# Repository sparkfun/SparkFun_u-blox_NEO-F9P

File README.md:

SparkFun GNSS-RTK L1/L5 Breakout - NEO-F9P (Qwiic)
========================================

[*SparkFun GNSS-RTK L1/L5 Breakout - NEO-F9P (Qwiic) (GPS-23288)*](https://www.sparkfun.com/products/23288)

The SparkFun GNSS-RTK L1/L5 Breakout - NEO-F9P (Qwiic) is a high-precision GNSS board with equally impressive configuration options. The NEO-F9P is an upgrade to the NEO-M8P and utilizes the L1/L5 bands instead of the L1/L2 bands. Utilizing the L5 band, the NEO-F9P delivers improved performance under challenging urban environments because the L5 signals fall within the protected ARNS (aeronautical radio navigation service) frequency band. This band is less subject to RF interference.

The NEO-F9P module is a powerful 184-channel u-blox F9 engine GNSS receiver, meaning it can receive signals from the GPS, GLONASS, Galileo, and BeiDou constellations with 10mm, three-dimensional accuracy! That's right; such accuracy can be achieved with an RTK navigation solution when used with a correction source. With this board, you will be able to know where your (or any object's) X, Y, and Z location is within roughly the width of your fingernail! The module supports the concurrent reception of four GNSS systems. This module features a survey-in mode, allowing the module to become a base station and produce RTCM 3.x correction data.

We've included a rechargeable backup battery to keep the latest module configuration and satellite data available for up to two weeks. This battery helps 'warm-start' the module, decreasing the time-to-first-fix dramatically from a cold start of ~27s down to a hot start of ~3s. The battery will maintain RTC and GNSS orbit data without being connected to power for plenty of time. We have included an SMA connector for a secure connection.

The GNSS-RTK even has five communications ports, which are all active simultaneously: USB-C (which enumerates as a COM port), UART1 (with 3.3V TTL), UART2 for RTCM reception (with 3.3V TTL), I<sup>2</sup>C, and SPI. Utilizing our handy Qwiic system, no soldering is required to connect it to the rest of your system. However, we still have broken out 0.1"-spaced pins if you prefer a breadboard.

u-blox-based GPS products are configurable using the popular but dense Windows program u-center. Many different functions can be configured on the NEO-F9P: baud rates, update rates, geofencing, spoofing detection, external interrupts, SBAS/D-GNSS, increasing the high precision RTK solution to 20Hz, etc. All of this can be done within the SparkFun Arduino Library!

Our extensive [Arduino Library for u-blox modules](https://github.com/sparkfun/SparkFun_u-blox_GNSS_v3) makes reading and controlling the GNSS-RTK over our [Qwiic Connect System](https://www.sparkfun.com/qwiic) easy. Leave NMEA behind! Start using a much lighter-weight binary interface and give your microcontroller a break. The SparkFun Arduino library shows how to read latitude, longitude, even heading, and speed over I<sup>2</sup>C without constant serial polling.

Repository Contents
-------------------

* **/Hardware** - Eagle design files (.brd, .sch)

Documentation
--------------

* [**Installing an Arduino Library Guide**](https://learn.sparkfun.com/tutorials/installing-an-arduino-library) - Basic information on how to install an Arduino library.
* **[Library](https://github.com/sparkfun/SparkFun_u-blox_GNSS_v3/)** - Arduino library for the NEO-F9P.
* **[Hookup Guide](http://docs.sparkfun.com/SparkFun_u-blox_NEO-F9P/)** - Basic hookup guide for the NEO-F9P breakout board.

Product Versions
----------------

* [GPS-23288](https://www.sparkfun.com/products/23288) - Initial release

Version History
---------------
* v1.1 - Initial release

License Information
-------------------

This product is _**open source**_!

Please review the LICENSE.md file for license information.

If you have any questions or concerns on licensing, please contact technical support on our [SparkFun forums](https://forum.sparkfun.com/viewforum.php?f=152).

Distributed as-is; no warranty is given.

- Your friends at SparkFun.

_<COLLABORATION CREDIT>_

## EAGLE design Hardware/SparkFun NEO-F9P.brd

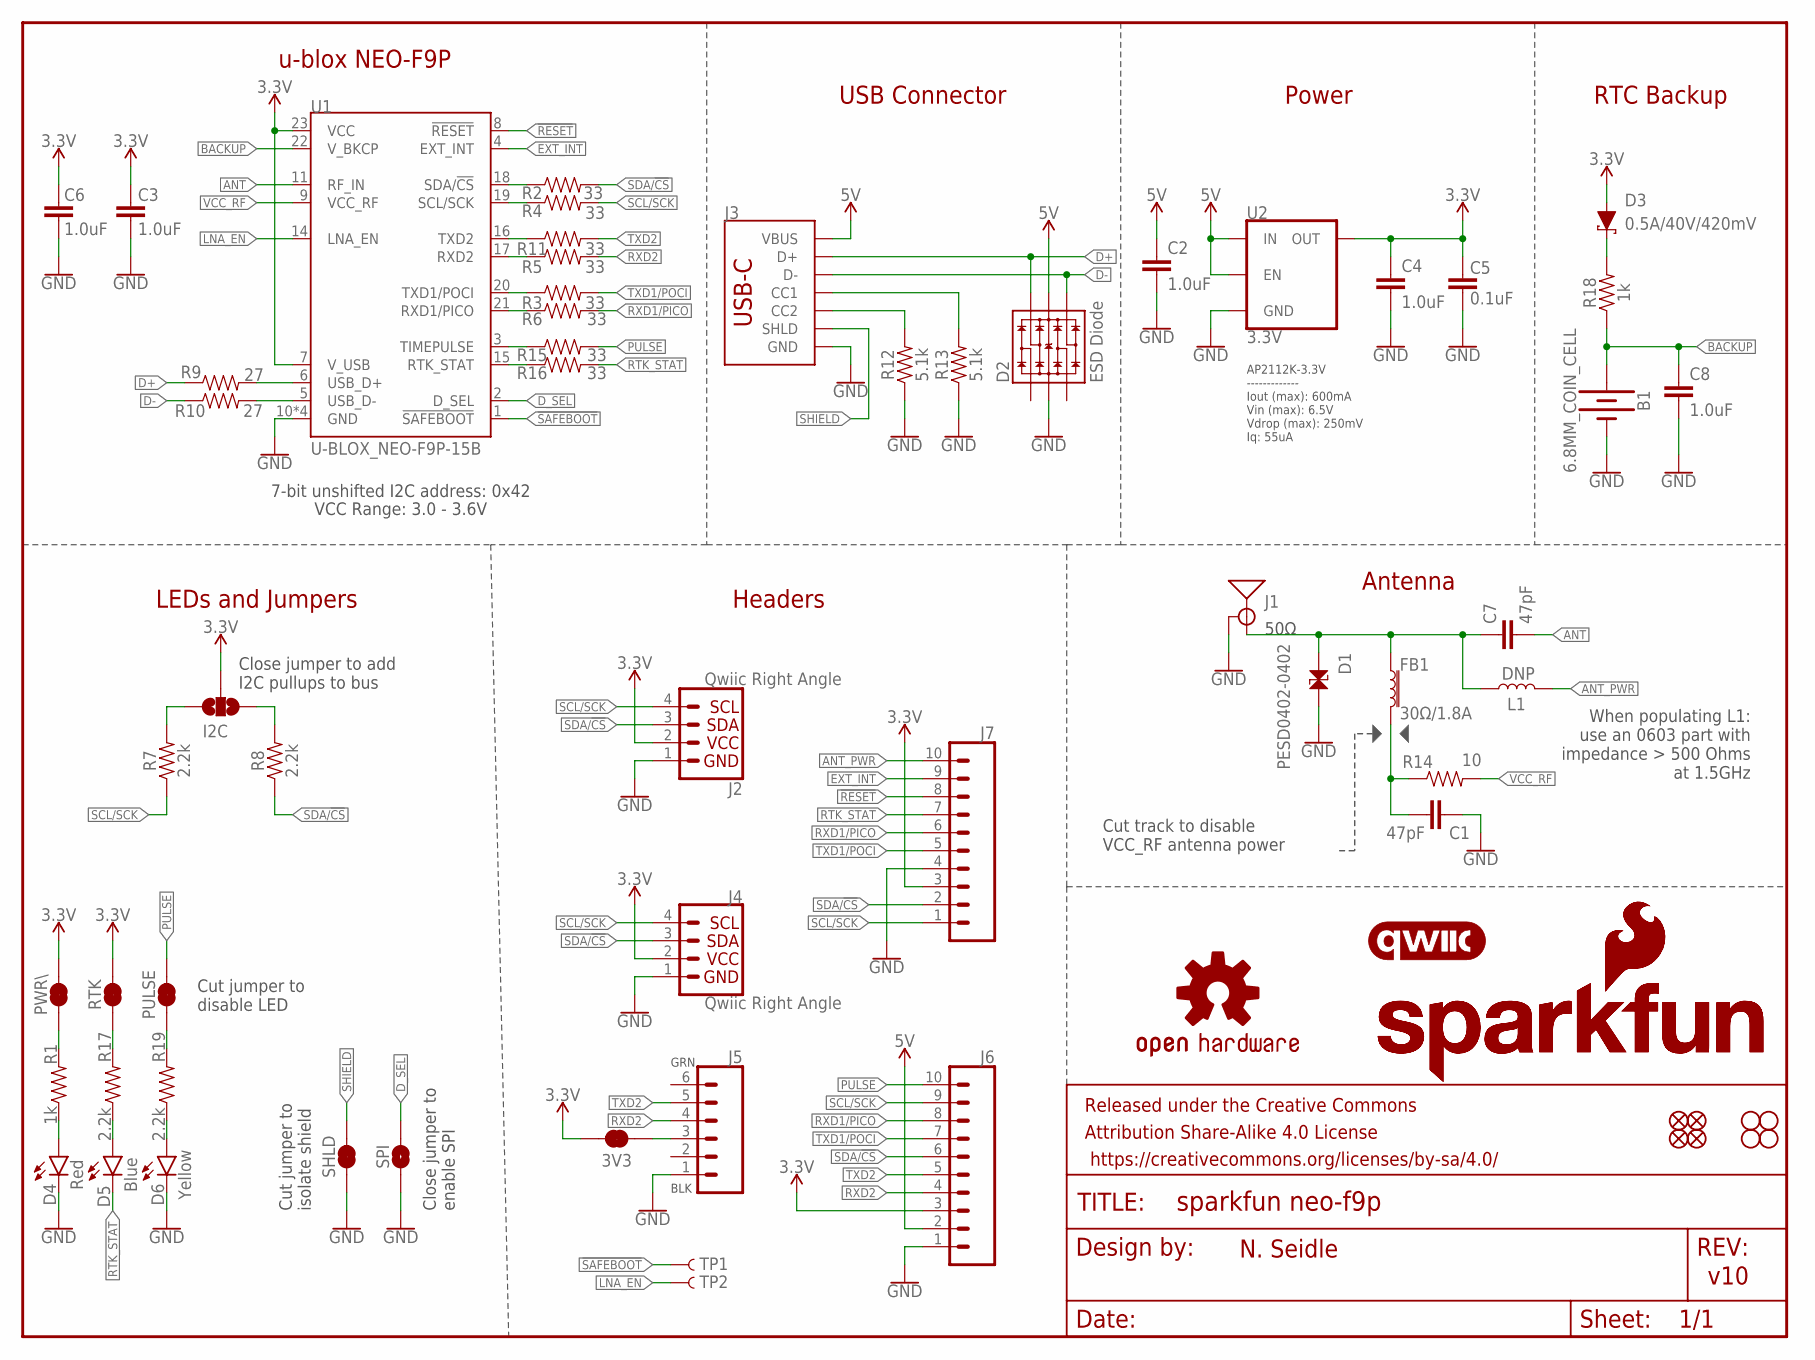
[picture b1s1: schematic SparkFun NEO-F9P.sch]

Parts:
3V3: JUMPER-SMT_2_NC_TRACE_SILK; SMT-JUMPER_2_NC_TRACE_SILK
B1: 6.8MM_COIN_CELL; ML414H_IV01E
C1, C7: 47pF; 0603
C2, C3, C4, C6, C8: 1.0uF; 0603
C5: 0.1uF; 0603
D1: PESD0402-0402; 0402
D2: ESD Diode; SOT-23-6
D3: 0.5A/40V/420mV; SOD-323
D4: Red; LED-0603
D5: Blue; LED-0603
D6: Yellow; LED-0603
FB1: 30Ω/1.8A; 0603
FRAME1: FRAME-LETTER; CREATIVE_COMMONS
I2C: JUMPER-SMT_3_NO_SILK; SMT-JUMPER_3_NO_SILK
J1: ANTENNA-SMA-GROUNDEDEDGE_SMA; SMA-EDGE
J2, J4: Qwiic Right Angle; JST04_1MM_RA
J3: USB_C_2-LAYER_PADS; USB-C-16P-2LAYER-PADS
J5: CONN_06NO_SILK_FEMALE_PTH; 1X06_NO_SILK
J6, J7: CONN_10NO_SILK_PTH_FEMALE; 1X10_NO_SILK
JP21, JP61, JP71, JP81: FIDUCIALUFIDUCIAL; MICRO-FIDUCIAL
JP31, JP41, JP91, JP101: STAND-OFF
L1: DNP; 0603_NO-CREAM
LOGO2: SFE_LOGO_NAME_FLAME.1_INCH; SFE_LOGO_NAME_FLAME_.1
LOGO3: SFE_LOGO_NAME_FLAME7_MM; SFE_LOGO_NAME_FLAME_7MM
LOGO4: OSHW-LOGOS; OSHW-LOGO-S
LOGO5: QWIIC_LOGO_5MM; QWIIC_5MM
PULSE: JUMPER-SMT_2_NC_TRACE_SILK; SMT-JUMPER_2_NC_TRACE_SILK
PWR\: JUMPER-SMT_2_NC_TRACE_SILK; SMT-JUMPER_2_NC_TRACE_SILK
R1, R18: 1k; 0603
R2, R3, R4, R5, R6, R11, R15, R16: 33; 0603
R7, R8, R17, R19: 2.2k; 0603
R9, R10: 27; 0603
R12, R13: 5.1k; 0603
R14: 10; 0603
RTK: JUMPER-SMT_2_NC_TRACE_SILK; SMT-JUMPER_2_NC_TRACE_SILK
SHLD: JUMPER-SMT_2_NC_TRACE_SILK; SMT-JUMPER_2_NC_TRACE_SILK
SPI: JUMPER-SMT_2_NO_SILK; SMT-JUMPER_2_NO_SILK
TP1, TP2: TEST-POINTPOGO_PTH; 1X01_NO_SILK
U1: U-BLOX_NEO-F9P-15B; NEO-M9N/M8T/M8U/D9S/F9P
U2: 3.3V; SOT23-5

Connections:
3.3V: 3V3.2, C3.1, C4.1, C5.2, C6.1, D3.A, I2C.2, J2.2, J4.2, J6.3, J7.3, PWR\.2, RTK.2, U1.7 (V_USB), U1.23 (VCC), U2.5 (OUT)
5V: C2.1, D2.5 (VCC), J3.VBUS1 (VBUS), J3.VBUS2 (VBUS), J6.2, U2.1 (IN), U2.3 (EN)
!RESET!: J7.8, U1.8 (!RESET!)
!SAFEBOOT!: TP1.1, U1.1 (!SAFEBOOT!)
ANT: C7.2, U1.11 (RF_IN)
ANT_PWR: J7.10, L1.2
ANT_VCC: C1.1, FB1.2, R14.1
BACKUP: B1.+, C8.1, R18.1, U1.22 (V_BKCP)
D+: D2.6 (IO4), J3.A6 (D+), J3.B6 (D+), R9.1
D-: D2.4 (IO3), J3.A7 (D-), J3.B7 (D-), R10.1
D_SEL: SPI.2, U1.2 (D_SEL)
EXT_INT: J7.9, U1.4 (EXT_INT)
GND: B1.-, C1.2, C2.2, C3.2, C4.2, C5.1, C6.2, C8.2, D1.2, D2.2 (VSS), D4.C, D6.C, J1.GND@0 (GND), J1.GND@1 (GND), J1.GND@2 (GND), J1.GND@3 (GND), J2.1, J3.GND, J3.GND2 (GND), J4.1, J5.1, J6.1, J7.4, R12.1, R13.1, SHLD.1, SPI.1, U1.10 (GND), U1.12 (GND), U1.13 (GND), U1.24 (GND), U2.2 (GND)
LNA_EN: TP2.1, U1.14 (LNA_EN)
unnamed: PWR\.1, R1.2
unnamed: R3.1, U1.20 (TXD1/POCI)
unnamed: R2.1, U1.18 (SDA/!CS!)
unnamed: R4.1, U1.19 (SCL/SCK)
unnamed: I2C.1, R8.2
unnamed: R6.1, U1.21 (RXD1/PICO)
unnamed: J3.B5 (CC2), R12.2
unnamed: I2C.3, R7.2
unnamed: J3.A5 (CC1), R13.2
unnamed: D4.A, R1.1
unnamed: R9.2, U1.6 (USB_D+)
unnamed: R10.2, U1.5 (USB_D-)
unnamed: 3V3.1, J5.3
unnamed: R11.1, U1.16 (TXD2)
unnamed: R5.1, U1.17 (RXD2)
unnamed: R15.1, U1.3 (TIMEPULSE)
unnamed: R16.1, U1.15 (RTK_STAT)
unnamed: D5.A, R17.1
unnamed: R17.2, RTK.1
unnamed: D3.C, R18.2
unnamed: D6.A, R19.1
unnamed: PULSE.1, R19.2
PULSE: J6.10, PULSE.2, R15.2
RTK_STAT: D5.C, J7.7, R16.2
RXD1/PICO: J6.8, J7.6, R6.2
RXD2: J5.4, J6.4, R5.2
SCL/SCK: J2.4, J4.4, J6.9, J7.1, R4.2, R7.1
SDA/!CS!: J2.3, J4.3, J6.6, J7.2, R2.2, R8.1
SHIELD: J3.SHLD1 (SHLD), J3.SHLD2 (SHLD), J3.SHLD3 (SHLD), J3.SHLD4 (SHLD), SHLD.2
SMA: C7.1, D1.1, FB1.1, J1.SIG (SIGNAL), L1.1
TXD1/POCI: J6.7, J7.5, R3.2
TXD2: J5.5, J6.5, R11.2
VCC_RF: R14.2, U1.9 (VCC_RF)

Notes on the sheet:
v10
7-bit unshifted I2C address: 0x42
Close jumper to add I2C pullups to bus
Cut jumper to disable LED
Close jumper to enable SPI
N. Seidle
Headers
LEDs and Jumpers
u-blox NEO-F9P
Antenna
USB Connector
VCC Range: 3.0 - 3.6V
BLK
GRN
Cut jumper to isolate shield
50Ω
Cut track to disable VCC_RF antenna power
When populating L1: use an 0603 part with impedance > 500 Ohms at 1.5GHz
AP2112K-3.3V ------------- Iout (max): 600mA Vin (max): 6.5V Vdrop (max): 250mV Iq: 55uA
RTC Backup
Power

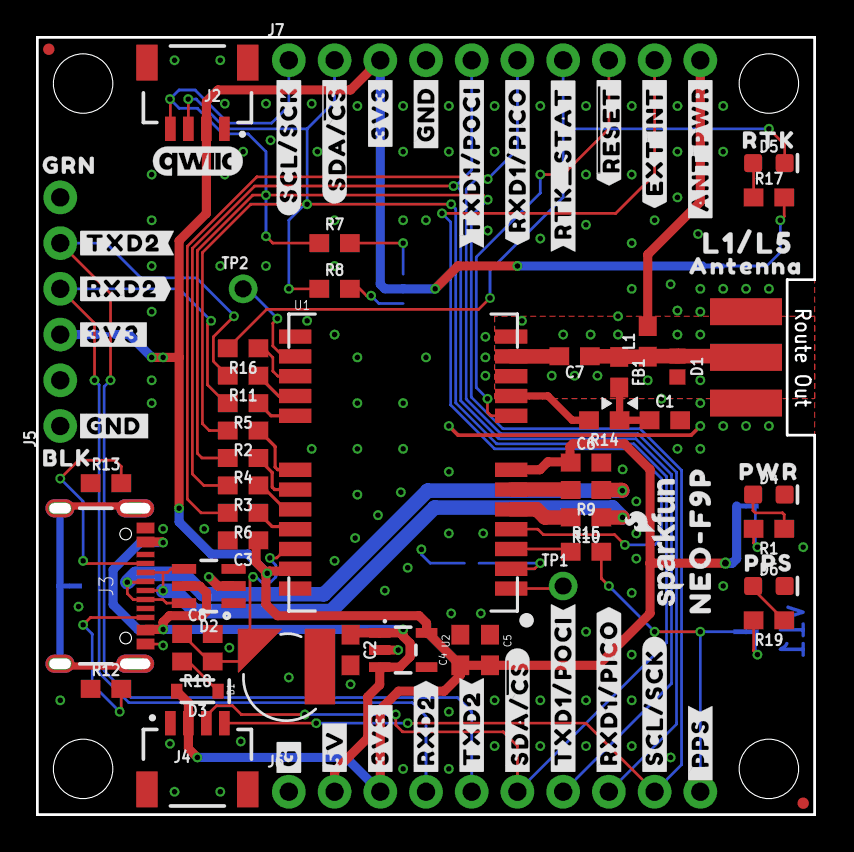
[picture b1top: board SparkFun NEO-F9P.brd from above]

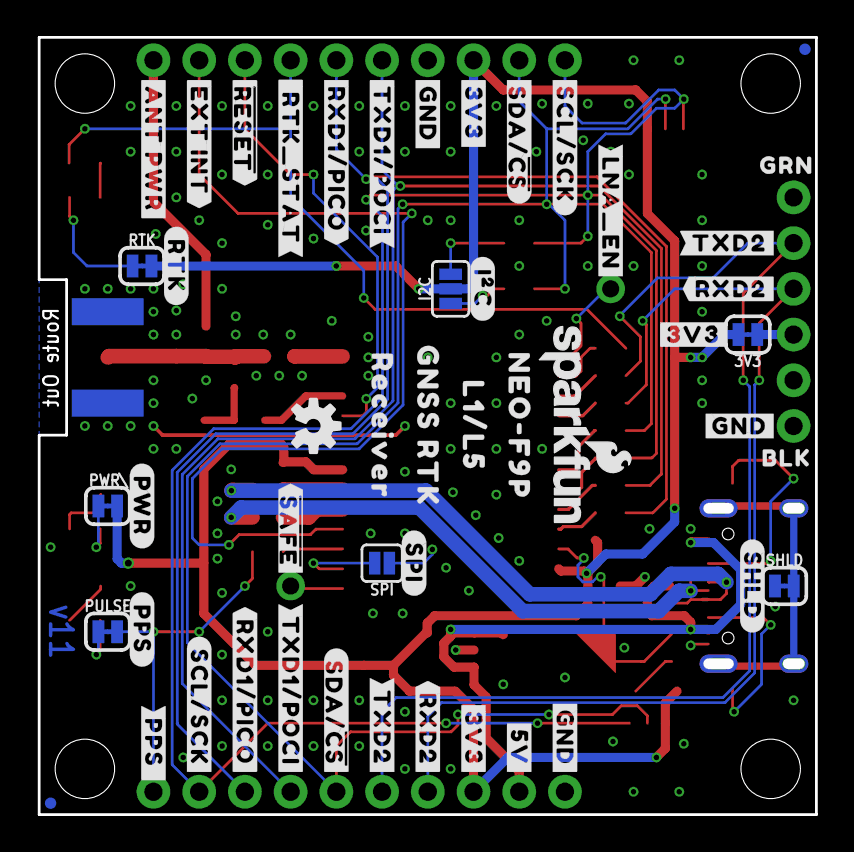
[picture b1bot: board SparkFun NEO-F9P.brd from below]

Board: 2 copper layers, 42.8 x 42.7 mm, 138 parts (49 on the bottom side), 47 nets.

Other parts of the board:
LOGO1: SPECIAL_INSTRUCTIONS-ORDERING; ORDERING_INSTRUCTIONS
U$2, U$3: #GND#0
U$4, U$5, U$6: #GND#1
U$7, U$8: #TXD2#0
U$9, U$10: #TXD2#3
U$11, U$12: #RXD2#0
U$13, U$15: #RXD2#3
U$14: #RTK_STAT#0
U$16, U$17: BLK0
U$18, U$19: GRN0
U$20: #5V#0
U$21: #5V#6
U$22, U$23, U$56, U$57: #3V3#0
U$24, U$25: #3V3#4
U$26, U$27: #SDA##CS##0
U$28, U$29: #SDA##CS##1
U$30, U$31: #TXD1#POCI#0
U$32, U$33: #TXD1#POCI#2
U$34, U$35: #RXD1#PICO#0
U$36, U$37: #RXD1#PICO#2
U$38: #_RTK_STAT#0
U$39, U$40: #SCL#SCK#0
U$41, U$42: #SCL#SCK#1
U$43: #RTK#0
U$44, U$64: L1#L50
U$45: ##RESET##0
U$46: ##RESET##1
U$47: #EXT_INT#0
U$48: #EXT_INT#1
U$49: PWR0
U$50: #PWR#0
U$51: #SPI#0
U$52: #I�C#0
U$53: #SHLD#0
U$54: RTK0
U$55: #G#0
U$58: #ANT_PWR#0
U$59: #ANT_PWR#1
U$60, U$61: NEO#F9P0
U$63: ANTENNA0
U$65: GNSS_RTK0
U$66: RECEIVER0
U$67: #LNA_EN#0
U$68: PPS0
U$69: #PPS#0
U$70: #_PPS#0
U$71: #PPS_#0
U$72: ##SAFE##0

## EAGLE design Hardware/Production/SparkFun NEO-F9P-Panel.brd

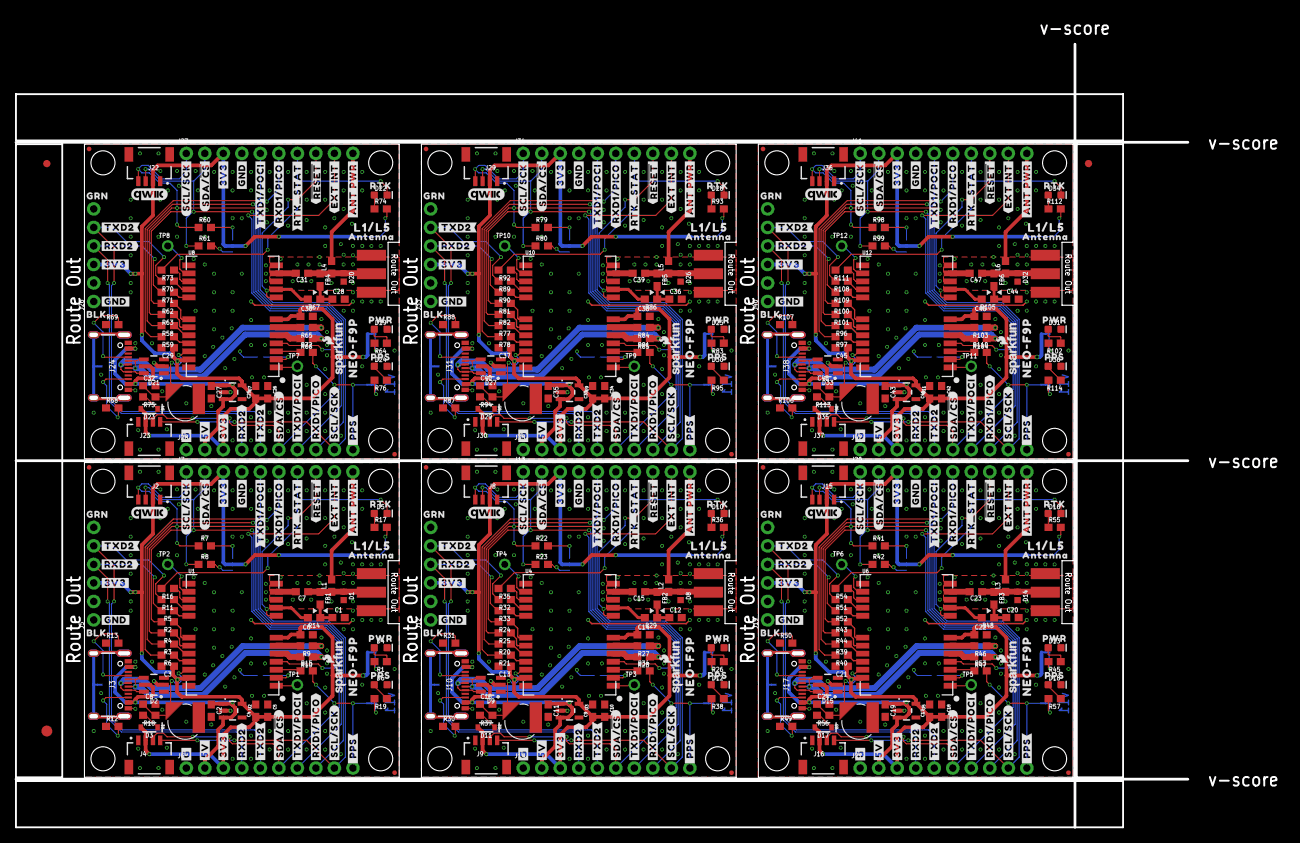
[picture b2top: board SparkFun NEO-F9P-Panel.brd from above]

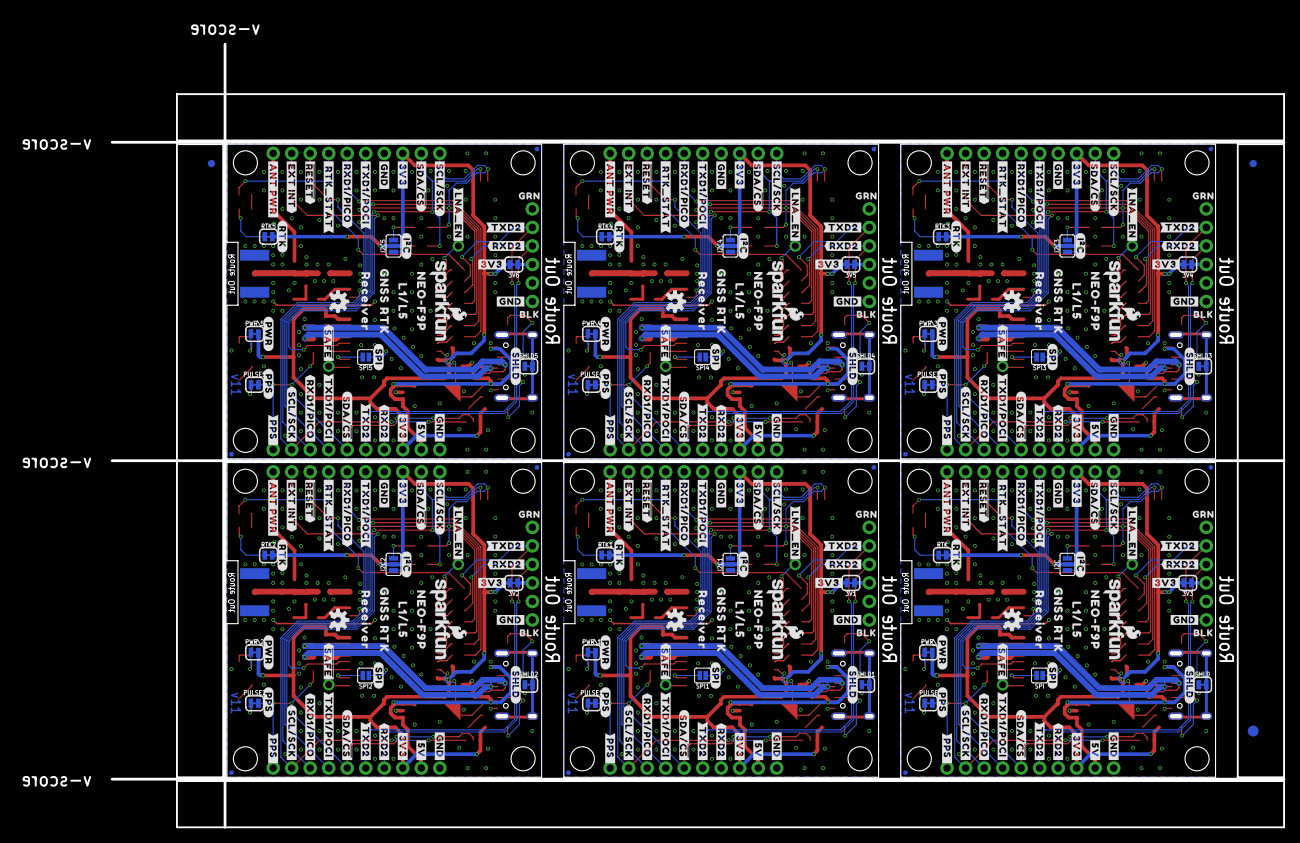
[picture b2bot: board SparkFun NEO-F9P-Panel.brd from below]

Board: 2 copper layers, 173.8 x 111.1 mm, 822 parts (297 on the bottom side), 282 nets.

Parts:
3V1, 3V2, 3V3, 3V4, 3V5, 3V6: JUMPER-SMT_2_NC_TRACE_SILK; SMT-JUMPER_2_NC_TRACE_SILK
B1, B2, B3, B4, B5, B6: 6.8MM_COIN_CELL; ML414H_IV01E
C1, C7, C12, C15, C20, C23, C28, C31, C36, C39, C44, C47: 47pF; 0603
C2, C3, C4, C6, C8, C9, C11, C13, C14, C16, C17, C19, C21, C22, C24, C25, C27, C29, C30, C32, C33, C35, C37, C38, C40, C41, C43, C45, C46, C48: 1.0uF; 0603
C5, C10, C18, C26, C34, C42: 0.1uF; 0603
D1, D8, D14, D20, D26, D32: PESD0402-0402; 0402
D2, D9, D15, D21, D27, D33: ESD Diode; SOT-23-6
D3, D11, D17, D23, D29, D35: 0.5A/40V/420mV; SOD-323
D4, D7, D13, D19, D25, D31: Red; LED-0603
D5, D10, D16, D22, D28, D34: Blue; LED-0603
D6, D12, D18, D24, D30, D36: Yellow; LED-0603
E$1, E$2, E$3, E$4: FIDUCIAL-1X2
E$5, E$6: FIDUCIAL-1.5X3
FB1, FB2, FB3, FB4, FB5, FB6: 30Ω/1.8A; 0603
I2C, I2C1, I2C2, I2C3, I2C4, I2C5: JUMPER-SMT_3_NO_SILK; SMT-JUMPER_3_NO_SILK
J1, J11, J18, J25, J32, J39: ANTENNA-SMA-GROUNDEDEDGE_SMA; SMA-EDGE
J2, J4, J8, J9, J15, J16, J22, J23, J29, J30, J36, J37: Qwiic Right Angle; JST04_1MM_RA
J3, J10, J17, J24, J31, J38: USB-C-16P-2LAYER-PADS
J5, J12, J19, J26, J33, J40: 1X06_NO_SILK
J6, J7, J13, J14, J20, J21, J27, J28, J34, J35, J41, J42: 1X10_NO_SILK
JP1, JP2, JP7, JP8, JP9, JP10, JP15, JP16, JP17, JP18, JP24, JP25, JP26, JP27, JP31, JP33, JP34, JP35, JP36, JP41, JP42, JP43, JP91, JP101: STAND-OFF
JP3, JP4, JP5, JP6, JP11, JP12, JP13, JP14, JP19, JP20, JP21, JP22, JP23, JP28, JP29, JP30, JP32, JP37, JP38, JP39, JP40, JP61, JP71, JP81: FIDUCIALUFIDUCIAL; MICRO-FIDUCIAL
L1, L2, L3, L4, L5, L6: DNP; 0603_NO-CREAM
LOGO1, LOGO3, LOGO9, LOGO13, LOGO17, LOGO21: SFE_LOGO_NAME_FLAME7_MM; SFE_LOGO_NAME_FLAME_7MM
LOGO2, LOGO6, LOGO10, LOGO14, LOGO18, LOGO22: SFE_LOGO_NAME_FLAME.1_INCH; SFE_LOGO_NAME_FLAME_.1
LOGO4, LOGO7, LOGO11, LOGO15, LOGO19, LOGO23: OSHW-LOGOS; OSHW-LOGO-S
LOGO5, LOGO8, LOGO12, LOGO16, LOGO20, LOGO24: QWIIC_LOGO_5MM; QWIIC_5MM
PULSE, PULSE1, PULSE2, PULSE3, PULSE4, PULSE5: JUMPER-SMT_2_NC_TRACE_SILK; SMT-JUMPER_2_NC_TRACE_SILK
PWR\, PWR\1, PWR\2, PWR\3, PWR\4, PWR\5: JUMPER-SMT_2_NC_TRACE_SILK; SMT-JUMPER_2_NC_TRACE_SILK
R1, R18, R26, R37, R45, R56, R64, R75, R83, R94, R102, R113: 1k; 0603
R2, R3, R4, R5, R6, R11, R15, R16, R20, R21, R24, R25, R32, R33, R34, R35, R39, R40, R43, R44, R51, R52, R53, R54, R58, R59, R62, R63, R70, R71, R72, R73, R77, R78, R81, R82, R89, R90, R91, R92, R96, R97, R100, R101, R108, R109, R110, R111: 33; 0603
R7, R8, R17, R19, R22, R23, R36, R38, R41, R42, R55, R57, R60, R61, R74, R76, R79, R80, R93, R95, R98, R99, R112, R114: 2.2k; 0603
R9, R10, R27, R28, R46, R47, R65, R66, R84, R85, R103, R104: 27; 0603
R12, R13, R30, R31, R49, R50, R68, R69, R87, R88, R106, R107: 5.1k; 0603
R14, R29, R48, R67, R86, R105: 10; 0603
RTK, RTK1, RTK2, RTK3, RTK4, RTK5: JUMPER-SMT_2_NC_TRACE_SILK; SMT-JUMPER_2_NC_TRACE_SILK
SHLD, SHLD1, SHLD2, SHLD3, SHLD4, SHLD5: JUMPER-SMT_2_NC_TRACE_SILK; SMT-JUMPER_2_NC_TRACE_SILK
SPI, SPI1, SPI2, SPI3, SPI4, SPI5: JUMPER-SMT_2_NO_SILK; SMT-JUMPER_2_NO_SILK
TP1, TP2, TP3, TP4, TP5, TP6, TP7, TP8, TP9, TP10, TP11, TP12: TEST-POINTPOGO_PTH; 1X01_NO_SILK
U1, U4, U6, U8, U10, U12: U-BLOX_NEO-F9P-15B; NEO-M9N/M8T/M8U/D9S/F9P
U2, U3, U5, U7, U9, U11: 3.3V; SOT23-5
U$1, U$2, U$3, U$62, U$141, U$142, U$211, U$212, U$281, U$282, U$351, U$352: #GND#0
U$4, U$5, U$6, U$73, U$74, U$75, U$143, U$144, U$145, U$213, U$214, U$215, U$283, U$284, U$285, U$353, U$354, U$355: #GND#1
U$7, U$8, U$76, U$77, U$146, U$147, U$216, U$217, U$286, U$287, U$356, U$357: #TXD2#0
U$9, U$10, U$78, U$79, U$148, U$149, U$218, U$219, U$288, U$289, U$358, U$359: #TXD2#3
U$11, U$12, U$80, U$81, U$150, U$151, U$220, U$221, U$290, U$291, U$360, U$361: #RXD2#0
U$13, U$15, U$82, U$83, U$152, U$153, U$222, U$223, U$292, U$293, U$362, U$363: #RXD2#3
U$14, U$125, U$195, U$265, U$335, U$405: #RTK_STAT#0
U$16, U$17, U$84, U$85, U$154, U$155, U$224, U$225, U$294, U$295, U$364, U$365: BLK0
U$18, U$19, U$86, U$87, U$156, U$157, U$226, U$227, U$296, U$297, U$366, U$367: GRN0
U$20, U$88, U$158, U$228, U$298, U$368: #5V#0
U$21, U$89, U$159, U$229, U$299, U$369: #5V#6
U$22, U$23, U$56, U$57, U$90, U$91, U$119, U$120, U$160, U$161, U$189, U$190, U$230, U$231, U$259, U$260, U$300, U$301, U$329, U$330, U$370, U$371, U$399, U$400: #3V3#0
U$24, U$25, U$92, U$93, U$162, U$163, U$232, U$233, U$302, U$303, U$372, U$373: #3V3#4
U$26, U$27, U$94, U$95, U$164, U$165, U$234, U$235, U$304, U$305, U$374, U$375: #SDA##CS##0
U$28, U$29, U$96, U$97, U$166, U$167, U$236, U$237, U$306, U$307, U$376, U$377: #SDA##CS##1
U$30, U$31, U$111, U$112, U$181, U$182, U$251, U$252, U$321, U$322, U$391, U$392: #TXD1#POCI#0
U$32, U$33, U$113, U$114, U$183, U$184, U$253, U$254, U$323, U$324, U$393, U$394: #TXD1#POCI#2
U$34, U$35, U$115, U$116, U$185, U$186, U$255, U$256, U$325, U$326, U$395, U$396: #RXD1#PICO#0
U$36, U$37, U$117, U$118, U$187, U$188, U$257, U$258, U$327, U$328, U$397, U$398: #RXD1#PICO#2
U$38, U$126, U$196, U$266, U$336, U$406: #_RTK_STAT#0
U$39, U$40, U$98, U$99, U$168, U$169, U$238, U$239, U$308, U$309, U$378, U$379: #SCL#SCK#0
U$41, U$42, U$100, U$101, U$170, U$171, U$240, U$241, U$310, U$311, U$380, U$381: #SCL#SCK#1
U$43, U$128, U$198, U$268, U$338, U$408: #RTK#0
U$44, U$64, U$129, U$131, U$199, U$201, U$269, U$271, U$339, U$341, U$409, U$411: L1#L50
U$45, U$102, U$172, U$242, U$312, U$382: ##RESET##0
U$46, U$103, U$173, U$243, U$313, U$383: ##RESET##1
U$47, U$104, U$174, U$244, U$314, U$384: #EXT_INT#0
U$48, U$105, U$175, U$245, U$315, U$385: #EXT_INT#1
U$49, U$106, U$176, U$246, U$316, U$386: PWR0
U$50, U$107, U$177, U$247, U$317, U$387: #PWR#0
U$51, U$108, U$178, U$248, U$318, U$388: #SPI#0
U$52, U$109, U$179, U$249, U$319, U$389: #I�C#0
U$53, U$110, U$180, U$250, U$320, U$390: #SHLD#0
U$54, U$127, U$197, U$267, U$337, U$407: RTK0
U$55, U$140, U$210, U$280, U$350, U$420: #G#0
U$58, U$121, U$191, U$261, U$331, U$401: #ANT_PWR#0
U$59, U$122, U$192, U$262, U$332, U$402: #ANT_PWR#1
U$60, U$61, U$123, U$124, U$193, U$194, U$263, U$264, U$333, U$334, U$403, U$404: NEO#F9P0
U$63, U$130, U$200, U$270, U$340, U$410: ANTENNA0
U$65, U$132, U$202, U$272, U$342, U$412: GNSS_RTK0
U$66, U$133, U$203, U$273, U$343, U$413: RECEIVER0
U$67, U$134, U$204, U$274, U$344, U$414: #LNA_EN#0
U$68, U$135, U$205, U$275, U$345, U$415: PPS0
U$69, U$136, U$206, U$276, U$346, U$416: #PPS#0
U$70, U$137, U$207, U$277, U$347, U$417: #_PPS#0
U$71, U$138, U$208, U$278, U$348, U$418: #PPS_#0
U$72, U$139, U$209, U$279, U$349, U$419: ##SAFE##0

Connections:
3.3V: 3V3.2, C3.1, C4.1, C5.2, C6.1, D3.A, I2C.2, J2.2, J4.2, J6.3, J7.3, PWR\.2, RTK.2, U1.7, U1.23, U2.5
3.3V1: 3V1.2, C9.1, C10.2, C13.1, C14.1, D11.A, I2C1.2, J8.2, J9.2, J13.3, J14.3, PWR\1.2, RTK1.2, U3.5, U4.7, U4.23
3.3V2: 3V2.2, C17.1, C18.2, C21.1, C22.1, D17.A, I2C2.2, J15.2, J16.2, J20.3, J21.3, PWR\2.2, RTK2.2, U5.5, U6.7, U6.23
3.3V3: 3V4.2, C25.1, C26.2, C29.1, C30.1, D23.A, I2C3.2, J22.2, J23.2, J27.3, J28.3, PWR\3.2, RTK3.2, U7.5, U8.7, U8.23
3.3V4: 3V5.2, C33.1, C34.2, C37.1, C38.1, D29.A, I2C4.2, J29.2, J30.2, J34.3, J35.3, PWR\4.2, RTK4.2, U9.5, U10.7, U10.23
3.3V5: 3V6.2, C41.1, C42.2, C45.1, C46.1, D35.A, I2C5.2, J36.2, J37.2, J41.3, J42.3, PWR\5.2, RTK5.2, U11.5, U12.7, U12.23
5V: C2.1, D2.5, J3.VBUS1, J3.VBUS2, J6.2, U2.1, U2.3
5V1: C11.1, D9.5, J10.VBUS1, J10.VBUS2, J14.2, U3.1, U3.3
5V2: C19.1, D15.5, J17.VBUS1, J17.VBUS2, J21.2, U5.1, U5.3
5V3: C27.1, D21.5, J24.VBUS1, J24.VBUS2, J28.2, U7.1, U7.3
5V4: C35.1, D27.5, J31.VBUS1, J31.VBUS2, J35.2, U9.1, U9.3
5V5: C43.1, D33.5, J38.VBUS1, J38.VBUS2, J42.2, U11.1, U11.3
!RESET!: J7.8, U1.8
!RESET!1: J13.8, U4.8
!RESET!2: J20.8, U6.8
!RESET!3: J27.8, U8.8
!RESET!4: J34.8, U10.8
!RESET!5: J41.8, U12.8
!SAFEBOOT!: TP1.1, U1.1
!SAFEBOOT!1: TP3.1, U4.1
!SAFEBOOT!2: TP5.1, U6.1
!SAFEBOOT!3: TP7.1, U8.1
!SAFEBOOT!4: TP9.1, U10.1
!SAFEBOOT!5: TP11.1, U12.1
ANT: C7.2, U1.11
ANT1: C15.2, U4.11
ANT2: C23.2, U6.11
ANT3: C31.2, U8.11
ANT4: C39.2, U10.11
ANT5: C47.2, U12.11
ANT_PWR: J7.10, L1.2
ANT_PWR1: J13.10, L2.2
ANT_PWR2: J20.10, L3.2
ANT_PWR3: J27.10, L4.2
ANT_PWR4: J34.10, L5.2
ANT_PWR5: J41.10, L6.2
ANT_VCC: C1.1, FB1.2, R14.1
ANT_VCC1: C12.1, FB2.2, R29.1
ANT_VCC2: C20.1, FB3.2, R48.1
ANT_VCC3: C28.1, FB4.2, R67.1
ANT_VCC4: C36.1, FB5.2, R86.1
ANT_VCC5: C44.1, FB6.2, R105.1
BACKUP: B1.+, C8.1, R18.1, U1.22
BACKUP1: B2.+, C16.1, R37.1, U4.22
BACKUP2: B3.+, C24.1, R56.1, U6.22
BACKUP3: B4.+, C32.1, R75.1, U8.22
BACKUP4: B5.+, C40.1, R94.1, U10.22
BACKUP5: B6.+, C48.1, R113.1, U12.22
D+: D2.6, J3.A6, J3.B6, R9.1
D+1: D9.6, J10.A6, J10.B6, R27.1
D+2: D15.6, J17.A6, J17.B6, R46.1
D+3: D21.6, J24.A6, J24.B6, R65.1
D+4: D27.6, J31.A6, J31.B6, R84.1
D+5: D33.6, J38.A6, J38.B6, R103.1
D-: D2.4, J3.A7, J3.B7, R10.1
D-1: D9.4, J10.A7, J10.B7, R28.1
D-2: D15.4, J17.A7, J17.B7, R47.1
D-3: D21.4, J24.A7, J24.B7, R66.1
D-4: D27.4, J31.A7, J31.B7, R85.1
D-5: D33.4, J38.A7, J38.B7, R104.1
D_SEL: SPI.2, U1.2
D_SEL1: SPI1.2, U4.2
D_SEL2: SPI2.2, U6.2
D_SEL3: SPI3.2, U8.2
D_SEL4: SPI4.2, U10.2
D_SEL5: SPI5.2, U12.2
EXT_INT: J7.9, U1.4
EXT_INT1: J13.9, U4.4
EXT_INT2: J20.9, U6.4
EXT_INT3: J27.9, U8.4
EXT_INT4: J34.9, U10.4
EXT_INT5: J41.9, U12.4
GND: B1.-, C1.2, C2.2, C3.2, C4.2, C5.1, C6.2, C8.2, D1.2, D2.2, D4.C, D6.C, J1.GND@0, J1.GND@1, J1.GND@2, J1.GND@3, J2.1, J3.GND, J3.GND2, J4.1, J5.1, J6.1, J7.4, R12.1, R13.1, SHLD.1, SPI.1, U1.10, U1.12, U1.13, U1.24, U2.2
GND1: B2.-, C9.2, C10.1, C11.2, C12.2, C13.2, C14.2, C16.2, D7.C, D8.2, D9.2, D12.C, J8.1, J9.1, J10.GND, J10.GND2, J11.GND@0, J11.GND@1, J11.GND@2, J11.GND@3, J12.1, J13.4, J14.1, R30.1, R31.1, SHLD1.1, SPI1.1, U3.2, U4.10, U4.12, U4.13, U4.24
GND2: B3.-, C17.2, C18.1, C19.2, C20.2, C21.2, C22.2, C24.2, D13.C, D14.2, D15.2, D18.C, J15.1, J16.1, J17.GND, J17.GND2, J18.GND@0, J18.GND@1, J18.GND@2, J18.GND@3, J19.1, J20.4, J21.1, R49.1, R50.1, SHLD2.1, SPI2.1, U5.2, U6.10, U6.12, U6.13, U6.24
GND3: B4.-, C25.2, C26.1, C27.2, C28.2, C29.2, C30.2, C32.2, D19.C, D20.2, D21.2, D24.C, J22.1, J23.1, J24.GND, J24.GND2, J25.GND@0, J25.GND@1, J25.GND@2, J25.GND@3, J26.1, J27.4, J28.1, R68.1, R69.1, SHLD3.1, SPI3.1, U7.2, U8.10, U8.12, U8.13, U8.24
GND4: B5.-, C33.2, C34.1, C35.2, C36.2, C37.2, C38.2, C40.2, D25.C, D26.2, D27.2, D30.C, J29.1, J30.1, J31.GND, J31.GND2, J32.GND@0, J32.GND@1, J32.GND@2, J32.GND@3, J33.1, J34.4, J35.1, R87.1, R88.1, SHLD4.1, SPI4.1, U9.2, U10.10, U10.12, U10.13, U10.24
GND5: B6.-, C41.2, C42.1, C43.2, C44.2, C45.2, C46.2, C48.2, D31.C, D32.2, D33.2, D36.C, J36.1, J37.1, J38.GND, J38.GND2, J39.GND@0, J39.GND@1, J39.GND@2, J39.GND@3, J40.1, J41.4, J42.1, R106.1, R107.1, SHLD5.1, SPI5.1, U11.2, U12.10, U12.12, U12.13, U12.24
LNA_EN: TP2.1, U1.14
LNA_EN1: TP4.1, U4.14
LNA_EN2: TP6.1, U6.14
LNA_EN3: TP8.1, U8.14
LNA_EN4: TP10.1, U10.14
LNA_EN5: TP12.1, U12.14
unnamed: PWR\.1, R1.2
unnamed: R3.1, U1.20
unnamed: R2.1, U1.18
unnamed: R4.1, U1.19
unnamed: I2C.1, R8.2
unnamed: R6.1, U1.21
unnamed: J3.B5, R12.2
unnamed: I2C.3, R7.2
unnamed: J3.A5, R13.2
unnamed: D4.A, R1.1
unnamed: R9.2, U1.6
unnamed: R10.2, U1.5
unnamed: 3V3.1, J5.3
unnamed: R11.1, U1.16
unnamed: R5.1, U1.17
unnamed: R15.1, U1.3
unnamed: R16.1, U1.15
unnamed: D5.A, R17.1
unnamed: R17.2, RTK.1
unnamed: D3.C, R18.2
unnamed: D6.A, R19.1
unnamed: PULSE.1, R19.2
unnamed: I2C1.1, R23.2
unnamed: I2C1.3, R22.2
unnamed: D7.A, R26.1
unnamed: R27.2, U4.6
unnamed: R28.2, U4.5
unnamed: PWR\1.1, R26.2
unnamed: J10.B5, R30.2
unnamed: J10.A5, R31.2
unnamed: R32.1, U4.16
unnamed: R33.1, U4.17
unnamed: R20.1, U4.20
unnamed: R21.1, U4.21
unnamed: R24.1, U4.18
unnamed: R25.1, U4.19
unnamed: 3V1.1, J12.3
unnamed: R34.1, U4.3
unnamed: R35.1, U4.15
unnamed: D10.A, R36.1
unnamed: R36.2, RTK1.1
unnamed: D11.C, R37.2
unnamed: D12.A, R38.1
unnamed: PULSE1.1, R38.2
unnamed: I2C2.1, R42.2
unnamed: I2C2.3, R41.2
unnamed: D13.A, R45.1
unnamed: R46.2, U6.6
unnamed: R47.2, U6.5
unnamed: PWR\2.1, R45.2
unnamed: J17.B5, R49.2
unnamed: J17.A5, R50.2
unnamed: R51.1, U6.16
unnamed: R52.1, U6.17
unnamed: R39.1, U6.20
unnamed: R40.1, U6.21
unnamed: R43.1, U6.18
unnamed: R44.1, U6.19
unnamed: 3V2.1, J19.3
unnamed: R53.1, U6.3
unnamed: R54.1, U6.15
unnamed: D16.A, R55.1
unnamed: R55.2, RTK2.1
unnamed: D17.C, R56.2
unnamed: D18.A, R57.1
unnamed: PULSE2.1, R57.2
unnamed: I2C3.1, R61.2
unnamed: I2C3.3, R60.2
unnamed: D19.A, R64.1
unnamed: R65.2, U8.6
unnamed: R66.2, U8.5
unnamed: PWR\3.1, R64.2
unnamed: J24.B5, R68.2
unnamed: J24.A5, R69.2
unnamed: R70.1, U8.16
unnamed: R71.1, U8.17
unnamed: R58.1, U8.20
unnamed: R59.1, U8.21
unnamed: R62.1, U8.18
unnamed: R63.1, U8.19
unnamed: 3V4.1, J26.3
unnamed: R72.1, U8.3
unnamed: R73.1, U8.15
unnamed: D22.A, R74.1
unnamed: R74.2, RTK3.1
unnamed: D23.C, R75.2
unnamed: D24.A, R76.1
unnamed: PULSE3.1, R76.2
unnamed: I2C4.1, R80.2
unnamed: I2C4.3, R79.2
unnamed: D25.A, R83.1
unnamed: R84.2, U10.6
unnamed: R85.2, U10.5
unnamed: PWR\4.1, R83.2
unnamed: J31.B5, R87.2
unnamed: J31.A5, R88.2
unnamed: R89.1, U10.16
unnamed: R90.1, U10.17
unnamed: R77.1, U10.20
unnamed: R78.1, U10.21
unnamed: R81.1, U10.18
unnamed: R82.1, U10.19
unnamed: 3V5.1, J33.3
unnamed: R91.1, U10.3
unnamed: R92.1, U10.15
unnamed: D28.A, R93.1
unnamed: R93.2, RTK4.1
unnamed: D29.C, R94.2
unnamed: D30.A, R95.1
unnamed: PULSE4.1, R95.2
unnamed: I2C5.1, R99.2
unnamed: I2C5.3, R98.2
unnamed: D31.A, R102.1
unnamed: R103.2, U12.6
unnamed: R104.2, U12.5
unnamed: PWR\5.1, R102.2
unnamed: J38.B5, R106.2
unnamed: J38.A5, R107.2
unnamed: R108.1, U12.16
unnamed: R109.1, U12.17
unnamed: R96.1, U12.20
unnamed: R97.1, U12.21
unnamed: R100.1, U12.18
unnamed: R101.1, U12.19
unnamed: 3V6.1, J40.3
unnamed: R110.1, U12.3
unnamed: R111.1, U12.15
unnamed: D34.A, R112.1
unnamed: R112.2, RTK5.1
unnamed: D35.C, R113.2
unnamed: D36.A, R114.1
unnamed: PULSE5.1, R114.2
PULSE: J6.10, PULSE.2, R15.2
PULSE1: J14.10, PULSE1.2, R34.2
PULSE2: J21.10, PULSE2.2, R53.2
PULSE3: J28.10, PULSE3.2, R72.2
PULSE4: J35.10, PULSE4.2, R91.2
PULSE5: J42.10, PULSE5.2, R110.2
RTK_STAT: D5.C, J7.7, R16.2
RTK_STAT1: D10.C, J13.7, R35.2
RTK_STAT2: D16.C, J20.7, R54.2
RTK_STAT3: D22.C, J27.7, R73.2
RTK_STAT4: D28.C, J34.7, R92.2
RTK_STAT5: D34.C, J41.7, R111.2
RXD1: J12.4, J14.4, R33.2
RXD1/PICO: J6.8, J7.6, R6.2
RXD1/PICO1: J13.6, J14.8, R21.2
RXD1/PICO2: J20.6, J21.8, R40.2
RXD1/PICO3: J27.6, J28.8, R59.2
RXD1/PICO4: J34.6, J35.8, R78.2
RXD1/PICO5: J41.6, J42.8, R97.2
RXD2: J5.4, J6.4, R5.2
RXD3: J19.4, J21.4, R52.2
RXD4: J26.4, J28.4, R71.2
RXD5: J33.4, J35.4, R90.2
RXD6: J40.4, J42.4, R109.2
SCL/SCK: J2.4, J4.4, J6.9, J7.1, R4.2, R7.1
SCL/SCK1: J8.4, J9.4, J13.1, J14.9, R22.1, R25.2
SCL/SCK2: J15.4, J16.4, J20.1, J21.9, R41.1, R44.2
SCL/SCK3: J22.4, J23.4, J27.1, J28.9, R60.1, R63.2
SCL/SCK4: J29.4, J30.4, J34.1, J35.9, R79.1, R82.2
SCL/SCK5: J36.4, J37.4, J41.1, J42.9, R98.1, R101.2
SDA/!CS!: J2.3, J4.3, J6.6, J7.2, R2.2, R8.1
SDA/!CS!1: J8.3, J9.3, J13.2, J14.6, R23.1, R24.2
SDA/!CS!2: J15.3, J16.3, J20.2, J21.6, R42.1, R43.2
SDA/!CS!3: J22.3, J23.3, J27.2, J28.6, R61.1, R62.2
SDA/!CS!4: J29.3, J30.3, J34.2, J35.6, R80.1, R81.2
SDA/!CS!5: J36.3, J37.3, J41.2, J42.6, R99.1, R100.2
SHIELD: J3.SHLD1, J3.SHLD2, J3.SHLD3, J3.SHLD4, SHLD.2
SHIELD1: J10.SHLD1, J10.SHLD2, J10.SHLD3, J10.SHLD4, SHLD1.2
SHIELD2: J17.SHLD1, J17.SHLD2, J17.SHLD3, J17.SHLD4, SHLD2.2
SHIELD3: J24.SHLD1, J24.SHLD2, J24.SHLD3, J24.SHLD4, SHLD3.2
SHIELD4: J31.SHLD1, J31.SHLD2, J31.SHLD3, J31.SHLD4, SHLD4.2
SHIELD5: J38.SHLD1, J38.SHLD2, J38.SHLD3, J38.SHLD4, SHLD5.2
SMA: C7.1, D1.1, FB1.1, J1.SIG, L1.1
SMA1: C15.1, D8.1, FB2.1, J11.SIG, L2.1
SMA2: C23.1, D14.1, FB3.1, J18.SIG, L3.1
SMA3: C31.1, D20.1, FB4.1, J25.SIG, L4.1
SMA4: C39.1, D26.1, FB5.1, J32.SIG, L5.1
SMA5: C47.1, D32.1, FB6.1, J39.SIG, L6.1
TXD1: J12.5, J14.5, R32.2
TXD1/POCI: J6.7, J7.5, R3.2
TXD1/POCI1: J13.5, J14.7, R20.2
TXD1/POCI2: J20.5, J21.7, R39.2
TXD1/POCI3: J27.5, J28.7, R58.2
TXD1/POCI4: J34.5, J35.7, R77.2
TXD1/POCI5: J41.5, J42.7, R96.2
TXD2: J5.5, J6.5, R11.2
TXD3: J19.5, J21.5, R51.2
TXD4: J26.5, J28.5, R70.2
TXD5: J33.5, J35.5, R89.2
TXD6: J40.5, J42.5, R108.2
VCC_RF: R14.2, U1.9
VCC_RF1: R29.2, U4.9
VCC_RF2: R48.2, U6.9
VCC_RF3: R67.2, U8.9
VCC_RF4: R86.2, U10.9
VCC_RF5: R105.2, U12.9

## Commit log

2023-07-20 Remove old files.
2023-07-20 Add LNA_EN label
2023-07-21 Add backup batt. Add PPS LED and PTH. Change silk. Fix RTK LED.
2023-07-27 Move R2.
2023-09-17 Adjust layout post design review.
2023-11-08 Increase version to v11
2023-12-08 Remove Artifacts from Cloning Repo
2023-12-22 Fix Minor Errors in Tutorial
    - Images out of sequence
    - Clarify which Arduino Library to use
    - Incorrect board dimensions
2024-01-05 Include Note about enabling L5 Band and Overriding Health Status Status and Add Arduino Example
2024-01-08 Deployed 18905f5 with MkDocs version: 1.5.3
2024-03-13 Update enable_l5_band_and_override_health_status.md
    fix broken link
2024-03-13 Deployed a400886 with MkDocs version: 1.5.3
2024-10-28 Add cookies
2024-10-29 Deployed 730b8ef with MkDocs version: 1.6.1
2025-02-20 Update introduction.md
    Updated missing image
2025-02-20 Deployed 81bc02d with MkDocs version: 1.6.1
2026-06-03 Deployed 90b8425 with MkDocs version: 1.6.1

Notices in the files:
parts and their libraries:
SparkFun-Resistors: Licensing: Creative Commons ShareAlike 4.0 International - https://creativecommons.org/licenses/by-sa/4.0
SparkFun-Aesthetics: Released under the Creative Commons Attribution Share-Alike 4.0 License
SparkFun-Aesthetics: https://creativecommons.org/licenses/by-sa/4.0
